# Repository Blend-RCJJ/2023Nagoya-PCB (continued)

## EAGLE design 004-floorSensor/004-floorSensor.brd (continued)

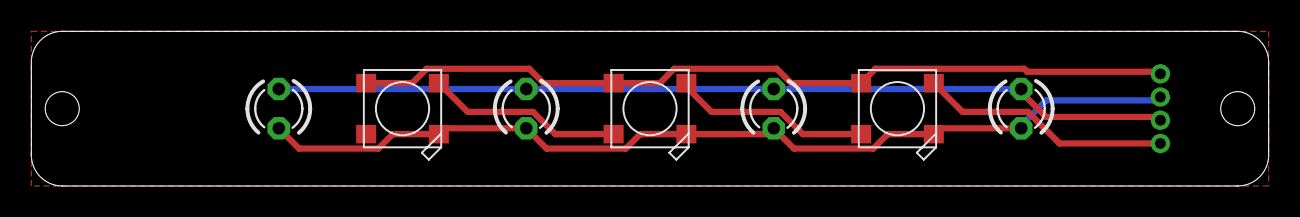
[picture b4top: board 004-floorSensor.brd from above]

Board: 2 copper layers, 80.0 x 10.0 mm, 8 parts (1 on the bottom side), 6 nets.

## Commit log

2022-11-11 基板進んだ
2022-11-12 ジャイロ配置
2022-11-12 UART配線完了
2022-11-12 ATmega消す
2022-11-13 ほぼ完了
2022-11-13 ひとまず完了
2022-11-15 シルク挿入完了
2022-11-26 #WeLoveSTM32
